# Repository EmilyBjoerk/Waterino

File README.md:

# Waterino

Waterino is a DIY multi-pot home watering system. Multiple pots are connected together by daisy chaining "nodes" together with a "root" node providing power, monitoring and water. The daisy chaining means that the chain can be re-ordered when moving pots around and that there is a minimal amount of wire-mess as opposed to a star-network.

Each "node" consists of an integrated moisture/temperature sensor and control logic, a pump/valve and an optional overflow sensor to safe guard from causing damage to the surrounding by watering too much.

The "root" node consists of a water reservoir, a Raspberry Pi and power delivery. The RPi monitors the nodes with heart-beat and listens for error reports over I2C, provides a web server with logging and monitoring and can be setup to send email alerts if an error is detected or if the water level in the reservoir is low.

# System Diagram

# Building on Debian
You'll need the following:

```sudo apt install build-essential git cmake clang clang-tools gcc-avr avr-libc libgmock-dev avrdude```

Building and running unit-tests:

```
cd firmware/test
mkdir build
cd build
cmake ..
make test
```

or ``` make && ./unit-tests ``` for a more detailed output.

Viewing code coverage of unit tests (first build as above):

```
cd firmware/test/build
../../codecov.sh [path_to_file.cpp]
```

Building binary:

```
cd firmware/src
mkdir build
cd build
cmake ..
make
```

Viewing binary stats (after building as above):

```
cd firmware/src/build
make size
make sizes
make disassemble && cat probe.lst
```

# Design
## Measurement
The Waterino uses capacitive soil moisture and temperature sensor integrated in the node PCB.

The PCB has a coplanar capacitor pattern where the soil is the dielectric. The capacitance of the coplanar capacitance depends on how much water is in the soil as the dielectric constant of water dominates that of other material in the soil. We measure the capacitance by charging it through a known resistance and measuring the time it takes to charge to a known value which gives the capacitance.

There is also a NTC thermistor inside the soil that we use to measure the soil temperature. The temperature is used for correcting the slight temperature dependency of the moisture-capacitance relation.

## Control
The user specifies the desired watering period in hours, the maximum time the pump may be active and the threshold moisture level when the pump will activate.
Each time the measured moisture drops below the threshold the pump activates. When the pump activates the onboard PID will measure the time from the last pump activation and use that in relation to the desired watering period to compute if it should give more or less water than it did last time.
Note that if a too long period is specified in relation to the water retaining capacity of the soil. It may be impossible to achieve the desired period. This would cause the PID give more and more water, causing the pot to eventually overflow. The maximum pump activation time is aimed at preventing this failure mode. 

## Logging
The node keeps a small in memory log of the last few measurements and other important information. The root will poll the nodes for their respective logs and keep a longer term history slice the data and serve it over HTTP.

## Communication
The node will print debug information over 5V UART at 38400 baud, 8 bits data, 0 parity, 1 stop bit.

The node is a i2c master and slave device. It can be addressed to read the log, set parameters and control the node in other ways. It can also send to the general call address and write a special magic sequence followed by it's own unique slave address, this acts as a mutex device for activating a pump so that only one pump is active at a time, thanks to the i2c bus arbitration and unique slave addresses. This is makes sure that the water preasure available is always the same for the pumps, one can imagine if all pumps were to activate at once, the feed line from the reservoir would probably not have enough flow rate and the later pumps in the daisy chain wouldn't get any water.

## Safety
There are a few things that can go wrong... First, it's an electronic device near water that can possibly output 12V@5A 60W of power. A number of safety measures are implemented to hopefully prevent the device from harming itself, you or the plants.
In no particular order:

* Nodes will detect if too much water was given to the plant by two electrodes which you put in the saucer below your plant. If these electrodes conduct electricity the pump is automatically killed and the node will limit the next pump activation to the time it took for it to overflow this time but make it 5% shorter. To prevent a fluke from limiting the pump activation to way too short times, it will carefully try to recover the maximum pump duration to the user set duration over time, backing off if it detects overflow again.
* It will detect if the water level in the reservoir is low and email you.
* It will prevent the time the pump is active from going below a minimum time.
* A PTC fuse on each node will trip if the power on that node shorts out, and a PTC fuse on the root will like wise protect the system.
* Nodes will detect upon restart if it was killed by the fuse tripping and emit a visual alert and push an error to the root. The node will resume normal operation after being power cycled once, allowing a human to inspect what went wrong before trying again.

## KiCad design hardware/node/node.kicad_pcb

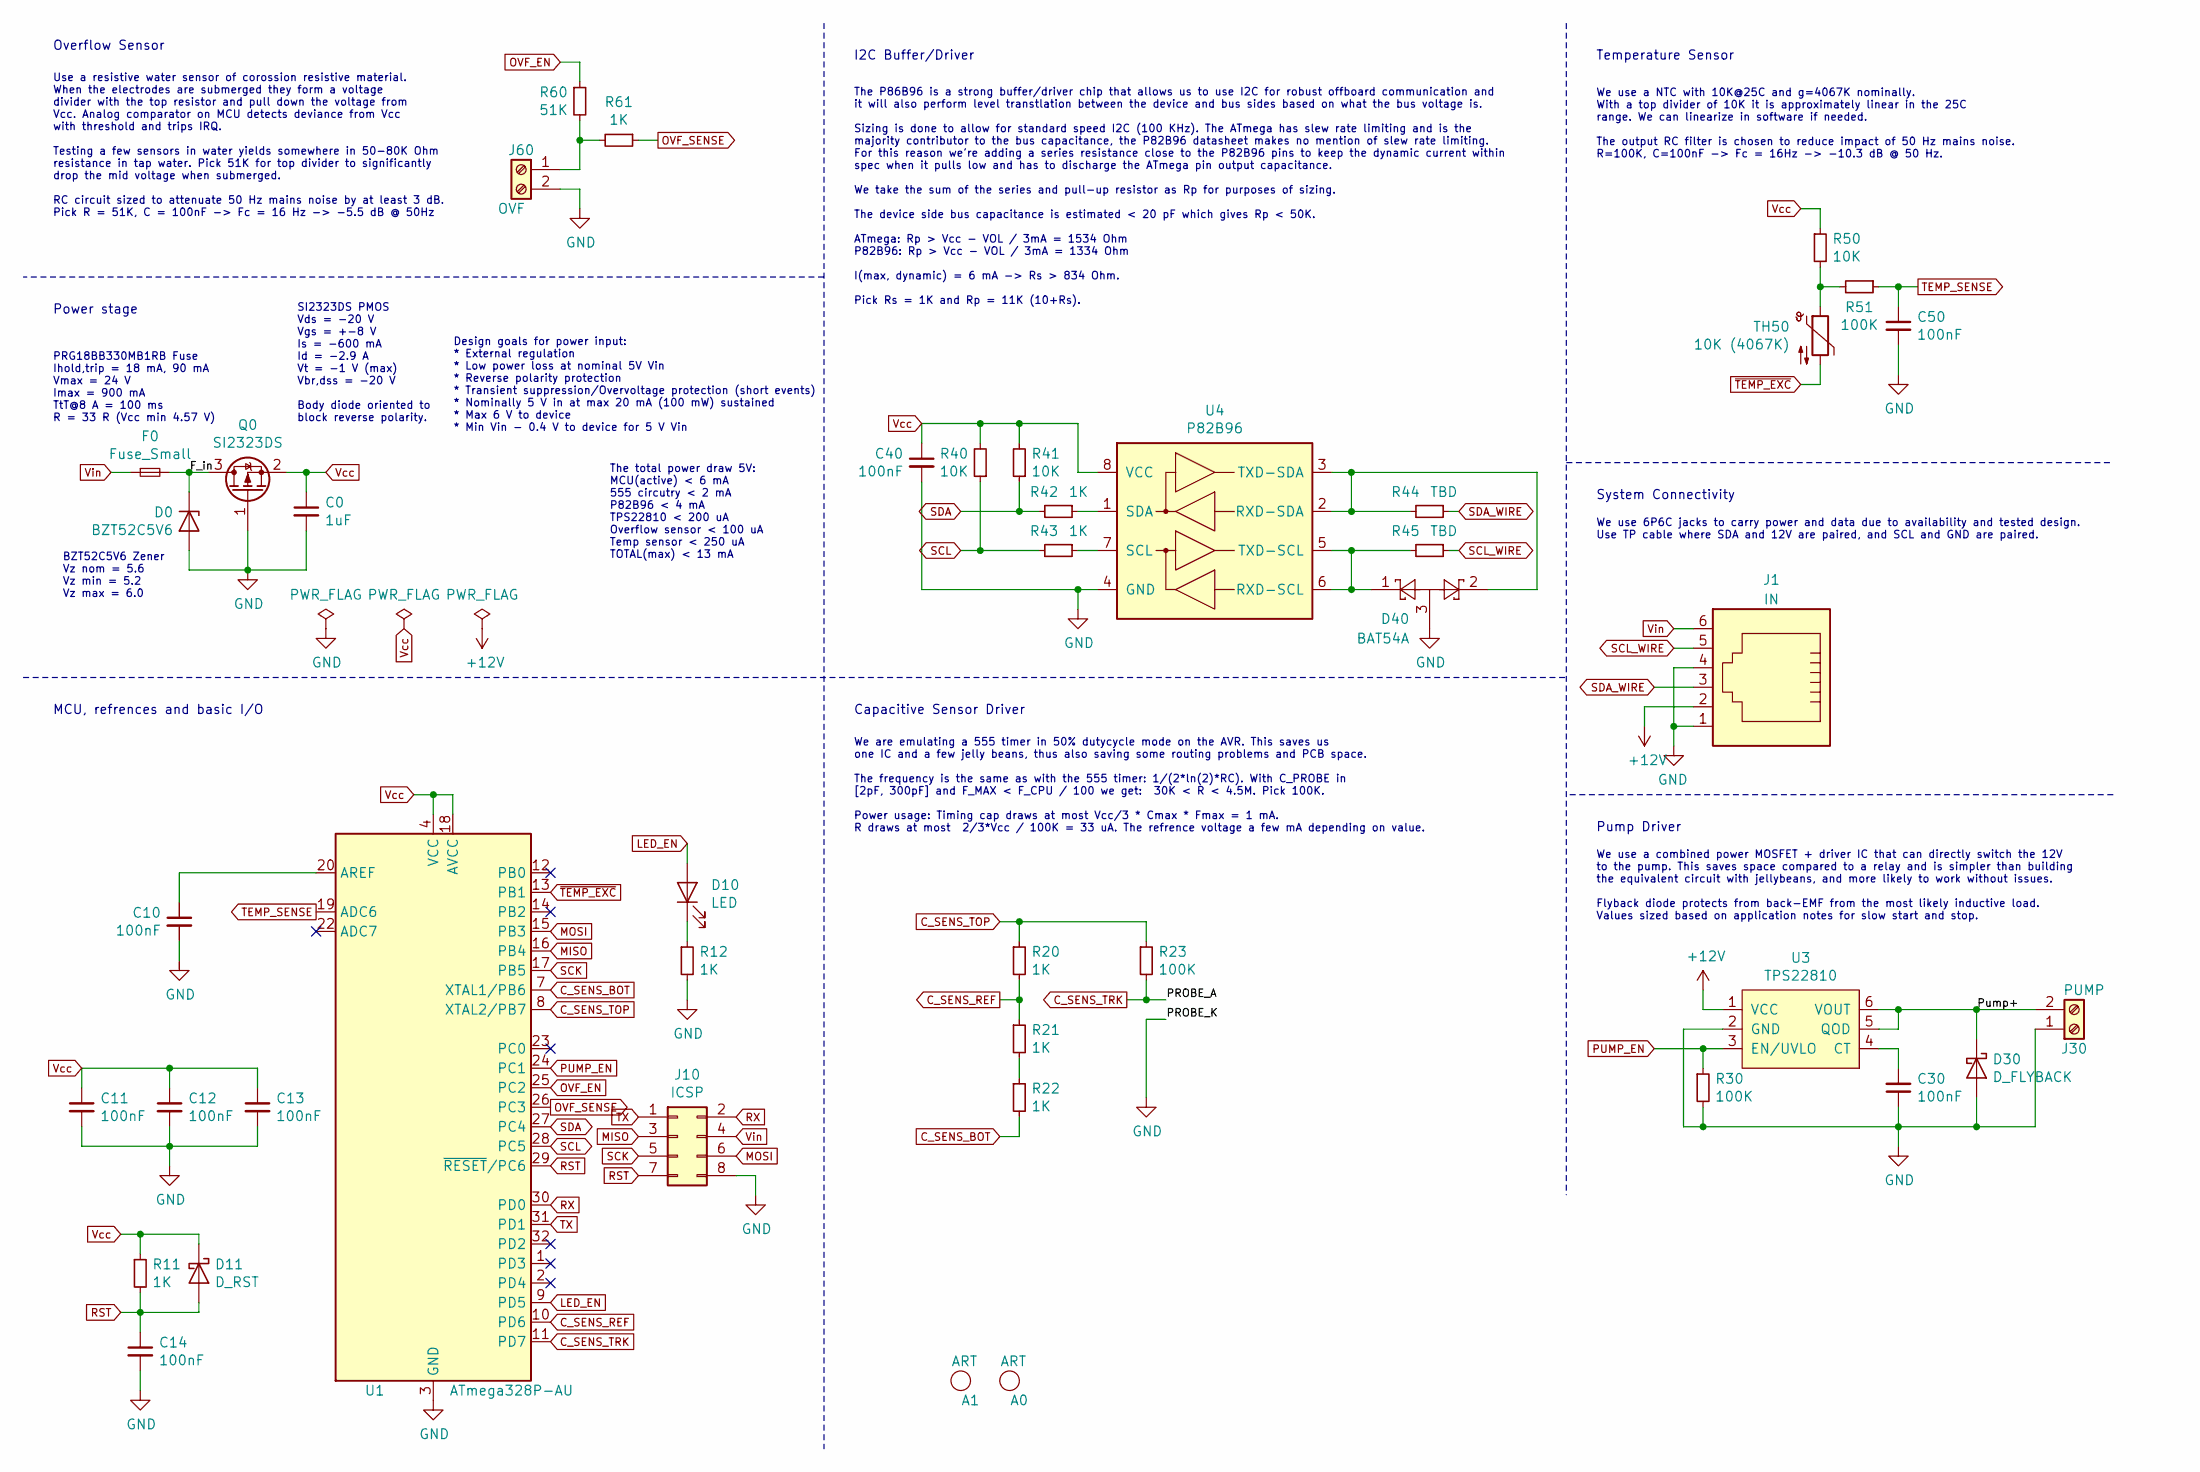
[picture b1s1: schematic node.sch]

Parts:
A0: ART; waterino_small_12_3mm
A1: ART; OSH_7_3mm
C0: 1uF; C_0603_1608Metric_Pad1.05x0.95mm_HandSolder
C10, C11, C12, C13, C14, C30, C40, C50: 100nF; C_0603_1608Metric_Pad1.05x0.95mm_HandSolder
D0: BZT52C5V6; D_SOD-123
D10: LED; LED_0603_1608Metric
D11: D_RST; D_SOD-123
D30: D_FLYBACK; D_SOD-123
D40: BAT54A; SOT-23
F0: Fuse_Small; Fuse_0603_1608Metric_Pad1.05x0.95mm_HandSolder
J1: IN; RJ12_Amphenol_54601
J10: ICSP; PinHeader_2x04_P2.54mm_Vertical
J30: PUMP; TerminalBlock_RND_205-00045_1x02_P5.00mm_Horizontal
J60: OVF; TerminalBlock_RND_205-00045_1x02_P5.00mm_Horizontal
Q0: SI2323DS; SOT-23W_Handsoldering
R11, R12, R20, R21, R22, R42, R43, R61: 1K; R_0603_1608Metric_Pad1.05x0.95mm_HandSolder
R23, R30, R51: 100K; R_0603_1608Metric_Pad1.05x0.95mm_HandSolder
R40, R41, R50: 10K; R_0603_1608Metric_Pad1.05x0.95mm_HandSolder
R44, R45: TBD; R_0603_1608Metric_Pad1.05x0.95mm_HandSolder
R60: 51K; R_0603_1608Metric_Pad1.05x0.95mm_HandSolder
TH50: 10K (4067K); R_0603_1608Metric_Pad1.05x0.95mm_HandSolder
U1: ATmega328P-AU; TQFP-32_7x7mm_P0.8mm
U3: TPS22810; SOT-23-6_Handsoldering
U4: P82B96; TSSOP-8_3x3mm_P0.65mm

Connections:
+12V: J1.2, U3.1 (VCC)
/F_in: D0.1 (K), F0.2, Q0.3 (D)
/Pump+: D30.1 (K), J30.2, U3.5 (QOD), U3.6 (VOUT)
C_SENS_BOT: R22.2, U1.7 (XTAL1/PB6)
C_SENS_REF: R20.2, R21.1, U1.10 (PD6)
C_SENS_TOP: R20.1, R23.1, U1.8 (XTAL2/PB7)
C_SENS_TRK: R23.2, U1.11 (PD7)
GND: C0.2, C10.2, C11.2, C12.2, C13.2, C14.2, C30.1, C40.2, C50.2, D0.2 (A), D30.2 (A), D40.3, J1.1, J1.4, J10.8, J30.1, J60.2, Q0.1 (G), R12.2, R30.2, U1.3 (GND), U1.5 (GND), U1.21 (GND), U3.2 (GND), U4.4 (GND)
LED_EN: D10.2 (A), U1.9 (PD5)
MISO: J10.3, U1.16 (PB4)
MOSI: J10.6, U1.15 (PB3)
unnamed: C10.1, U1.20 (AREF)
unnamed: C30.2, U3.4 (CT)
unnamed: D10.1 (K), R12.1
unnamed: D40.1, R45.2, U4.5 (TXD-SCL), U4.6 (RXD-SCL)
unnamed: D40.2, R44.2, U4.2 (RXD-SDA), U4.3 (TXD-SDA)
unnamed: J60.1, R60.2, R61.2
unnamed: R21.2, R22.1
unnamed: R42.1, U4.1 (SDA)
unnamed: R43.1, U4.7 (SCL)
unnamed: R50.2, R51.2, TH50.1
OVF_EN: R60.1, U1.25 (PC2)
OVF_SENSE: R61.1, U1.26 (PC3)
PUMP_EN: R30.1, U1.24 (PC1), U3.3 (EN/UVLO)
RST: C14.1, D11.2 (A), J10.7, R11.2, U1.29 (~RESET~/PC6)
RX: J10.2, U1.30 (PD0)
SCK: J10.5, U1.17 (PB5)
SCL: R40.1, R43.2, U1.28 (PC5)
SCL_WIRE: J1.5, R45.1
SDA: R41.1, R42.2, U1.27 (PC4)
SDA_WIRE: J1.3, R44.1
TEMP_SENSE: C50.1, R51.1, U1.19 (ADC6)
TX: J10.1, U1.31 (PD1)
Vcc: C0.1, C11.1, C12.1, C13.1, C40.1, D11.1 (K), Q0.2 (S), R11.1, R40.2, R41.2, R50.1, U1.4 (VCC), U1.6 (VCC), U1.18 (AVCC), U4.8 (VCC)
Vin: F0.1, J1.6, J10.4
~TEMP_EXC: TH50.2, U1.13 (PB1)

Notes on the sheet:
Power stage
Design goals for power input: * External regulation * Low power loss at nominal 5V Vin * Reverse polarity protection * Transient suppression/Overvoltage protection (short events) * Nominally 5 V in at max 20 mA (100 mW) sustained * Max 6 V to device * Min Vin - 0.4 V to device for 5 V Vin
BZT52C5V6 Zener Vz nom = 5.6 Vz min = 5.2 Vz max = 6.0
SI2323DS PMOS Vds = -20 V Vgs = +-8 V Is = -600 mA Id = -2.9 A Vt = -1 V (max) Vbr,dss = -20 V Body diode oriented to block reverse polarity.
PRG18BB330MB1RB Fuse Ihold,trip = 18 mA, 90 mA Vmax = 24 V Imax = 900 mA TtT@8 A = 100 ms R = 33 R (Vcc min 4.57 V)
We use 6P6C jacks to carry power and data due to availability and tested design. Use TP cable where SDA and 12V are paired, and SCL and GND are paired.
System Connectivity
Overflow Sensor
Use a resistive water sensor of corossion resistive material. When the electrodes are submerged they form a voltage divider with the top resistor and pull down the voltage from Vcc. Analog comparator on MCU detects deviance from Vcc with threshold and trips IRQ. Testing a few sensors in water yield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
Pump Driver
We use a combined power MOSFET + driver IC that can directly switch the 12V to the pump. This saves space compared to a relay and is simpler than building the equivalent circuit with jellybeans, and more likely to work without issues. Flyback diode protects from back-EMF from the most likely induct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
Temperature Sensor
We use a NTC with 10K@25C and g=4067K nominally. With a top divider of 10K it is approximately linear in the 25C range. We can linearize in software if needed. The output RC filter is chosen to reduce impact of 50 Hz mains noise. R=100K, C=100nF -> Fc = 16Hz -> -10.3 dB @ 50 Hz.
I2C Buffer/Driver
The P86B96 is a strong buffer/driver chip that allows us to use I2C for robust offboard communication and it will also perform level transtlation between the device and bus sides based on what the bus voltage is. Sizing is done to allow for standard speed I2C (100 KHz). The ATmega has slew rate lim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
Capacitive Sensor Driver
MCU, refrences and basic I/O
The total power draw 5V: MCU(active) < 6 mA 555 circutry < 2 mA P82B96 < 4 mA TPS22810 < 200 uA Overflow sensor < 100 uA Temp sensor < 250 uA TOTAL(max) < 13 mA
We are emulating a 555 timer in 50% dutycycle mode on the AVR. This saves us one IC and a few jelly beans, thus also saving some routing problems and PCB space. The frequency is the same as with the 555 timer: 1/(2*ln(2)*RC). With C_PROBE in [2pF, 300pF] and F_MAX < F_CPU / 100 we get: 30K < R < 4.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

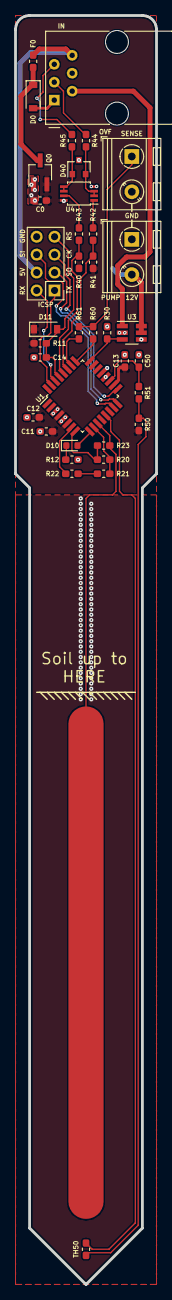
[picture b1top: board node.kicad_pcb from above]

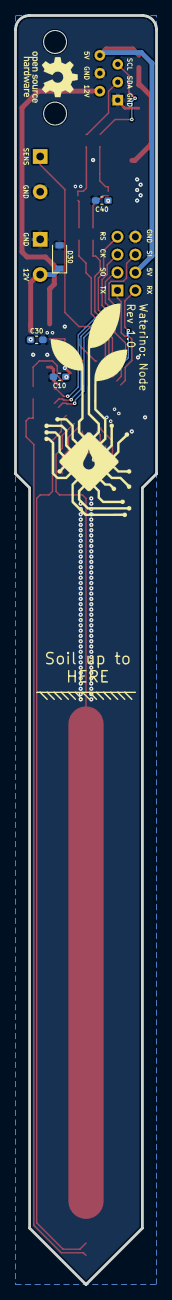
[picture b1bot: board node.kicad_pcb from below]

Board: 2 copper layers, 20.0 x 180.0 mm, 43 parts (6 on the bottom side), 36 nets.

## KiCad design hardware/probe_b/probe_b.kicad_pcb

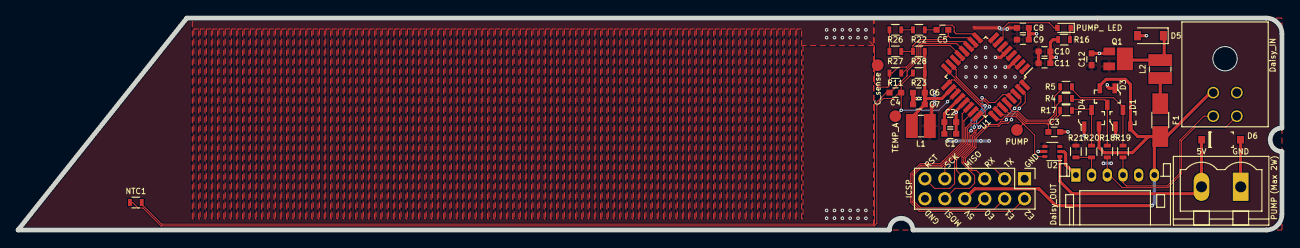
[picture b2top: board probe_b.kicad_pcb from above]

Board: 2 copper layers, 161.0 x 27.0 mm, 46 parts (0 on the bottom side), 37 nets.

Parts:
C1, C3, C6, C9, C10: 10nF; C_0603
C2, C4, C5, C7, C8, C11: 100nF; C_0603
C12: 1µF; C_0603
D1, D3, D4: BAT54S-7-F; SOT-23-3
D2: PUMP_ LED; D_0603
D5: BZT52C5V6; D_SOD-123
D6: MBR0520LT1G; SOD-123
F1: 0ZCJ0050FF2G; Fuse_SMD1206_HandSoldering
J1: ICSP; Pin_Header_Straight_2x06_Pitch2.54mm
J2: PUMP; Measurement_Point_Round-SMD-Pad_Small
J3: PUMP; PhoenixContact_MSTBVA-G_02x5.00mm_Vertical
J4: C_sense; Measurement_Point_Round-SMD-Pad_Small
J5: Daisy_OUT; JST_PH_S6B-PH-K_06x2.00mm_Angled
J6: Daisy_IN; Molex_Microfit3_Header_02x02_Angled_43045-040x
J7: TEMP_A; Measurement_Point_Round-SMD-Pad_Small
L1, L2: 10uH; 1210
NTC1: R; R_0603
Q1: SI2323DS; SOT-23-Power
R4, R5, R17, R18, R19, R20: 150R; R_0603
R11: 1M; R_0603
R16: 1K; R_0603
R21: 10K; R_0603
R22, R26, R27, R28: 100K; R_0603
R23: 15K; R_0603
U1: ATMEGA328P-AU; TQFP-32_7x7mm_Pitch0.8mm
U2: MIC94090; SOT-363_SC-70-6

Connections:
/Csense: J4.1, R11.2, U1.11
AVcc: C6.1, C7.1, L1.2, R23.1, R28.2, U1.18
DBG_A0: J1.6, U1.24
DBG_A1: J1.4, U1.23
DBG_A2: J1.2, U1.22
GND: C1.2, C2.2, C3.2, C6.2, C7.2, C8.2, C9.2, C10.2, C11.2, C12.2, D1.1, D3.1, D4.1, D5.2, D6.A, J1.1, J1.12, J3.1, J5.1, J5.5, J6.2, Q1.1, R16.2, U1.3, U1.5, U1.21, U2.2, U2.5
MISO: J1.7, U1.16
MOSI: J1.10, U1.15
unnamed: C1.1, C2.1, U1.20
unnamed: D1.3, R5.1, R19.2
unnamed: D2.1, R16.1
unnamed: D3.3, R4.1, R18.2
unnamed: D4.3, R17.1, R20.2
unnamed: D5.1, L2.2, Q1.3
unnamed: D6.K, J3.2, U2.1
unnamed: F1.2, L2.1
unnamed: J5.2, R20.1, R21.2
unnamed: J5.3, J6.4, R18.1
unnamed: J5.4, J6.3, R19.1
unnamed: R22.2, R26.1
unnamed: R26.2, R27.1
OVRFLW_SENSE: C3.1, R17.2, U1.26
PUMP: J2.1, U1.25, U2.6
PWRLED: D2.2, U1.7
RC_EN: R11.1, U1.12
RC_REF: C5.1, R27.2, R28.1, U1.10
RST: J1.11, U1.29
RX: J1.5, U1.30
SCK: J1.9, U1.17
SCL: R5.2, U1.28
SDA: R4.2, U1.27
TEMP+: C4.2, J7.1, NTC1.1, R23.2, U1.19
TX: J1.3, U1.31
Vcc: C8.1, C9.1, C10.1, C11.1, C12.1, L1.1, Q1.2, R21.1, U1.4, U1.6, U2.4
Vin: D1.2, D3.2, D4.2, F1.1, J1.8, J5.6, J6.1
~RC_EXC: C5.2, R22.1, U1.9
~TEMP_EXC: C4.1, NTC1.2, U1.13

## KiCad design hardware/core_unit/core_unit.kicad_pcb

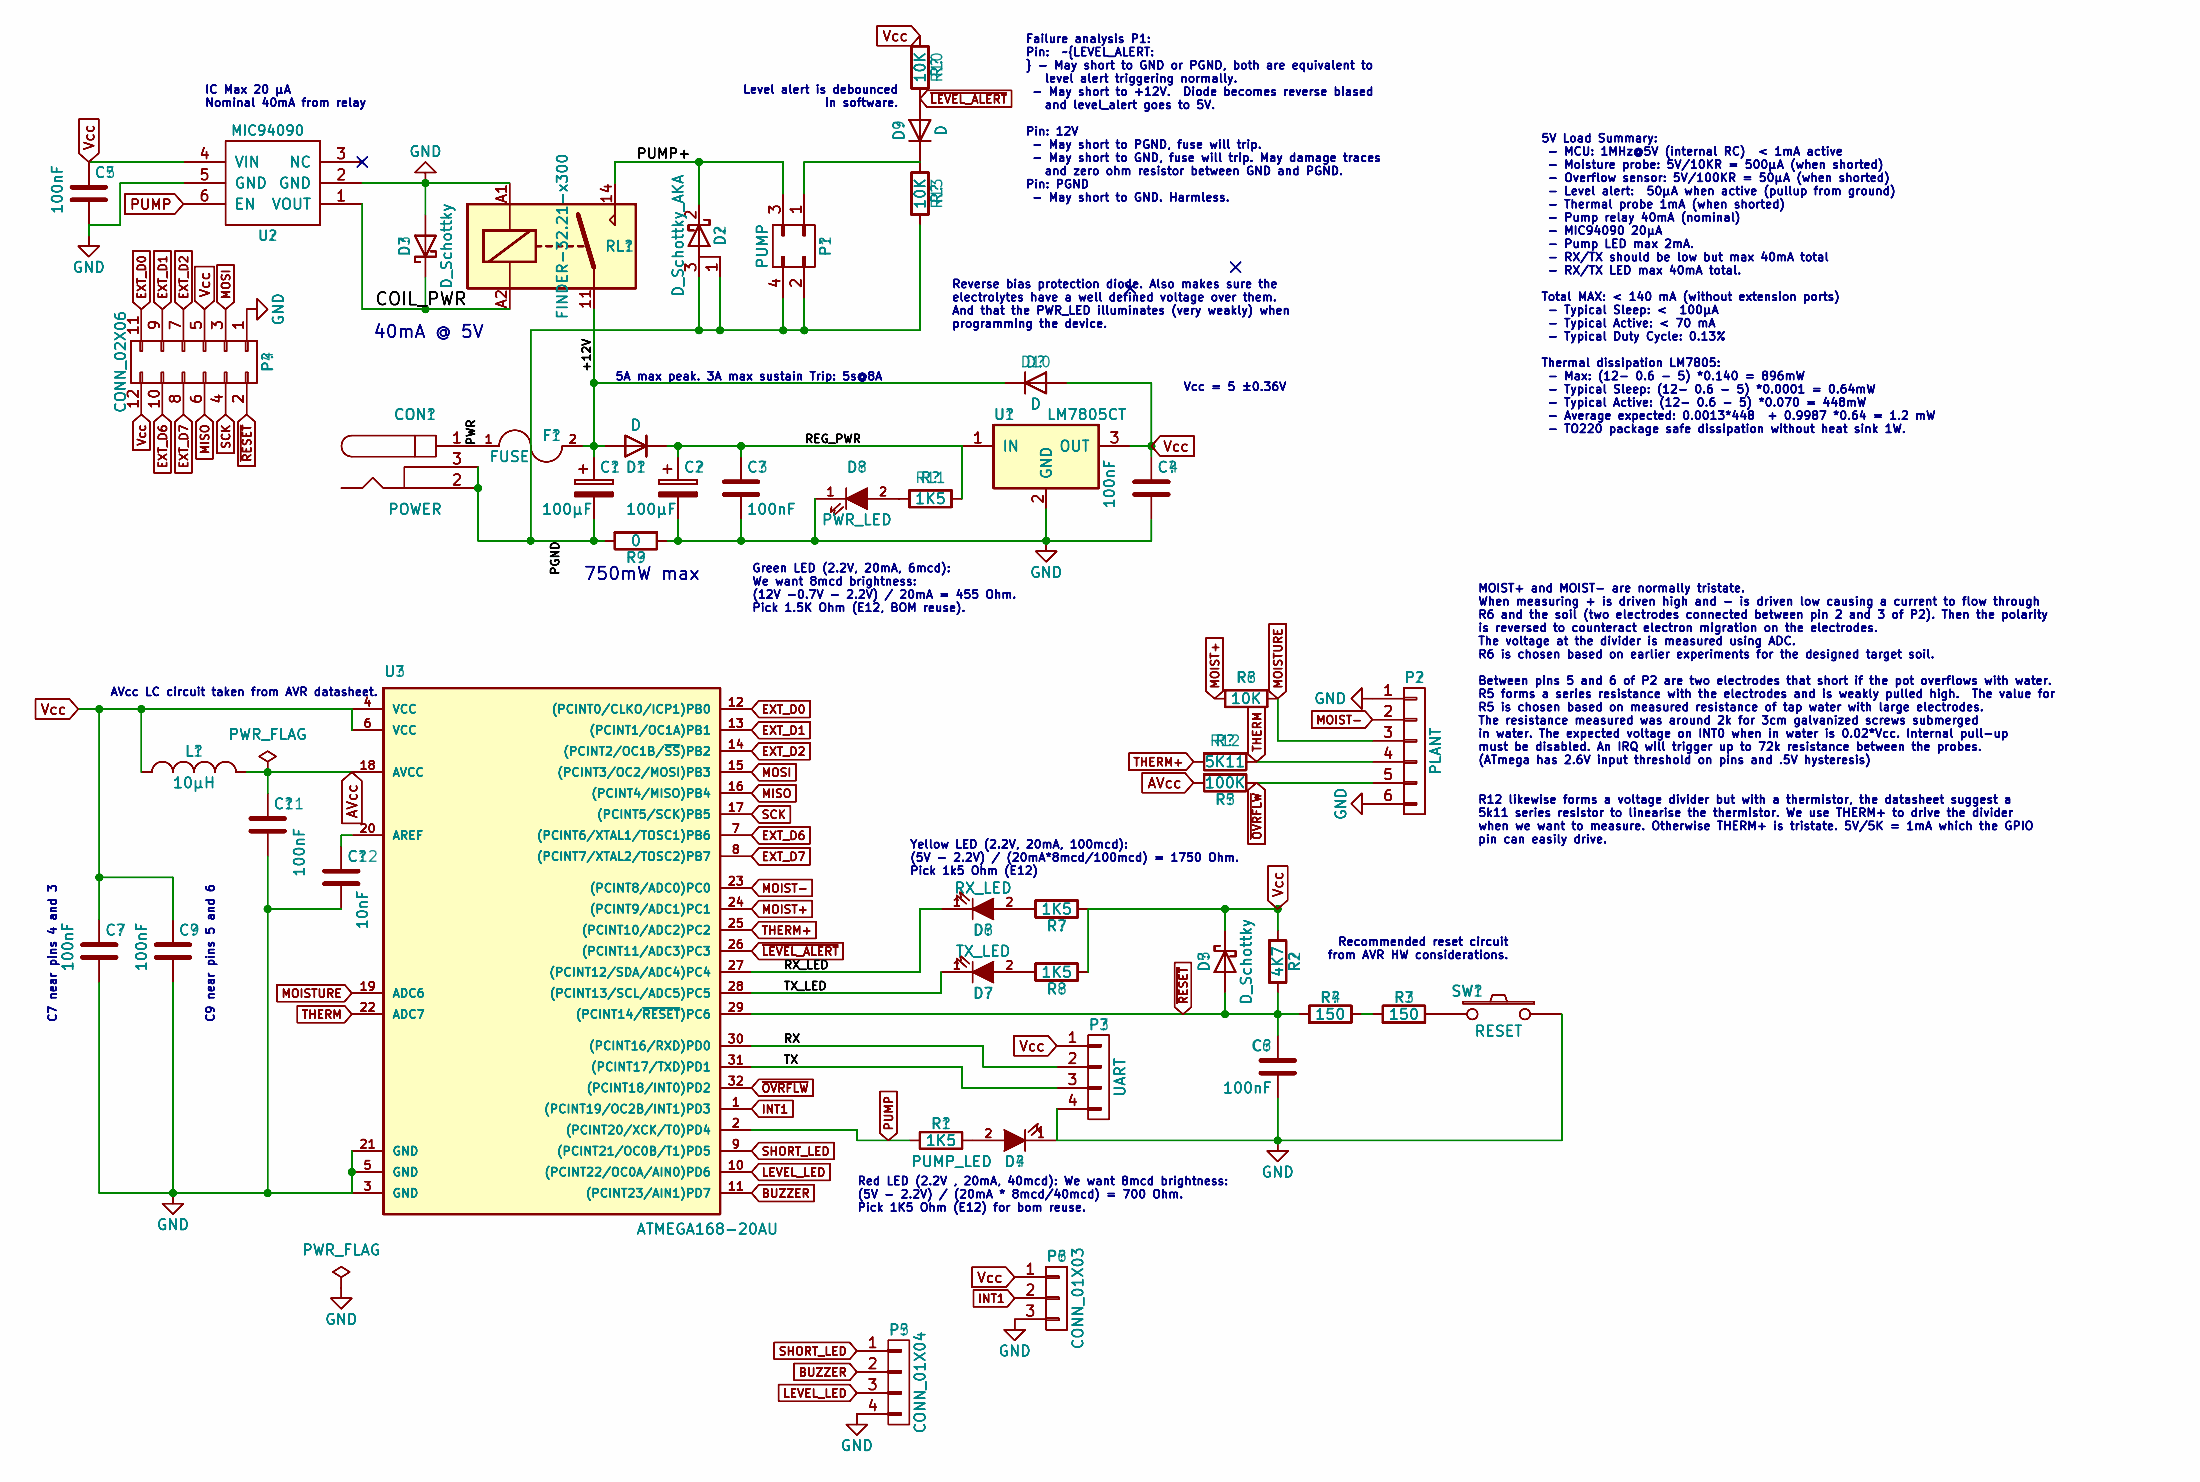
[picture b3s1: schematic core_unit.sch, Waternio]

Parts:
C1, C2: 100µF; CP_Elec_6.3x7.7
C3, C4, C5, C6, C7, C9, C11: 100nF; C_0603
C12: 10nF; C_0603
CON1: POWER; BARREL_JACK
D1, D9, D10: D; D_DO-41_SOD81_P7.62mm_Horizontal
D2: D_Schottky_AKA; TO-252-2_Rectifier
D3, D5: D_Schottky; D_SOD-123
D4: PUMP_LED; LED_0603
D6: RX_LED; LED_0603
D7: TX_LED; LED_0603
D8: PWR_LED; LED_0603
F1: FUSE; Fuse_SMD2920
L1: 10µH; L_Axial_L7.0mm_D3.3mm_P10.16mm_Horizontal_Fastron_MICC
P1: PUMP; Molex_Microfit3_Header_02x02_Angled_43045-040x
P2: PLANT; JST_PH_S6B-PH-K_06x2.00mm_Angled
P3: UART; Pin_Header_Straight_1x04_Pitch2.54mm
P4: CONN_02X06; Pin_Header_Straight_2x06_Pitch2.54mm
P5: CONN_01X04; Pin_Header_Straight_2x02_Pitch2.54mm
P6: CONN_01X03; Pin_Header_Straight_1x03_Pitch2.54mm
R1, R7, R8, R11: 1K5; R_0603
R2: 4K7; R_0603
R3, R4: 150; R_0603
R5: 100K; R_0603
R6, R10, R13: 10K; R_0603
R9: 0; R_2010
R12: 5K11; R_0603
RL1: FINDER-32.21-x300; Relay_SPST_Finder_32.21-x300
SW1: RESET; SW_PUSH_6mm
U1: LM7805CT; TO-220
U2: MIC94090; SOT-363_SC-70-6_Handsoldering
U3: ATMEGA168-20AU; TQFP-32_7x7mm_Pitch0.8mm

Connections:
/+12V: C1.1, D1.2 (A), D10.1 (K), F1.2, RL1.11
/COIL_PWR: D3.1 (K), RL1.A2, U2.1 (VOUT)
/PGND: C1.2, CON1.2, CON1.3, D2.1 (A), D2.3 (A), P1.2, P1.4, R9.2, R13.2
/PUMP+: D2.2 (K), P1.3, RL1.14
/PWR: CON1.1, F1.1
/REG_PWR: C2.1, C3.1, D1.1 (K), R11.1, U1.1 (IN)
/RX: P3.2, U3.30 ((PCINT16/RXD)PD0)
/RX_LED: D6.1 (K), U3.27 ((PCINT12/SDA/ADC4)PC4)
/TX: P3.3, U3.31 ((PCINT17/TXD)PD1)
/TX_LED: D7.1 (K), U3.28 ((PCINT13/SCL/ADC5)PC5)
AVcc: C11.1, L1.2, R5.2, U3.18 (AVCC)
BUZZER: P5.2, U3.11 ((PCINT23/AIN1)PD7)
EXT_D0: P4.11, U3.12 ((PCINT0/CLKO/ICP1)PB0)
EXT_D1: P4.9, U3.13 ((PCINT1/OC1A)PB1)
EXT_D2: P4.7, U3.14 ((PCINT2/OC1B/~SS~)PB2)
EXT_D6: P4.10, U3.7 ((PCINT6/XTAL1/TOSC1)PB6)
EXT_D7: P4.8, U3.8 ((PCINT7/XTAL2/TOSC2)PB7)
GND: C2.2, C3.2, C4.2, C5.2, C6.2, C7.2, C9.2, C11.2, C12.2, D3.2 (A), D4.1 (K), D8.1 (K), P2.1, P2.6, P3.4, P4.1, P5.4, P6.3, R9.1, RL1.A1, SW1.1, U1.2 (GND), U2.2 (GND), U2.5 (GND), U3.3 (GND), U3.5 (GND), U3.21 (GND)
INT1: P6.2, U3.1 ((PCINT19/OC2B/INT1)PD3)
LEVEL_LED: P5.3, U3.10 ((PCINT22/OC0A/AIN0)PD6)
MISO: P4.6, U3.16 ((PCINT4/MISO)PB4)
MOIST+: R6.1, U3.24 ((PCINT9/ADC1)PC1)
MOIST-: P2.2, U3.23 ((PCINT8/ADC0)PC0)
MOISTURE: P2.3, R6.2, U3.19 (ADC6)
MOSI: P4.3, U3.15 ((PCINT3/OC2/MOSI)PB3)
unnamed: C12.1, U3.20 (AREF)
unnamed: D4.2 (A), R1.2
unnamed: D6.2 (A), R7.2
unnamed: D7.2 (A), R8.2
unnamed: D8.2 (A), R11.2
unnamed: D9.1 (K), P1.1, R13.1
unnamed: R3.1, SW1.2
unnamed: R3.2, R4.1
PUMP: R1.1, U2.6 (EN), U3.2 ((PCINT20/XCK/T0)PD4)
SCK: P4.4, U3.17 ((PCINT5/SCK)PB5)
SHORT_LED: P5.1, U3.9 ((PCINT21/OC0B/T1)PD5)
THERM: P2.4, R12.1, U3.22 (ADC7)
THERM+: R12.2, U3.25 ((PCINT10/ADC2)PC2)
Vcc: C4.1, C5.1, C7.1, C9.1, D5.1 (K), D10.2 (A), L1.1, P3.1, P4.5, P4.12, P6.1, R2.2, R7.1, R8.1, R10.1, U1.3 (OUT), U2.4 (VIN), U3.4 (VCC), U3.6 (VCC)
~LEVEL_ALERT: D9.2 (A), R10.2, U3.26 ((PCINT11/ADC3)PC3)
~OVRFLW: P2.5, R5.1, U3.32 ((PCINT18/INT0)PD2)
~RESET: C6.1, D5.2 (A), P4.2, R2.1, R4.2, U3.29 ((PCINT14/~RESET~)PC6)

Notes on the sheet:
Yellow LED (2.2V, 20mA, 100mcd): (5V - 2.2V) / (20mA*8mcd/100mcd) = 1750 Ohm. Pick 1k5 Ohm (E12)
Green LED (2.2V, 20mA, 6mcd): We want 8mcd brightness: (12V -0.7V - 2.2V) / 20mA = 455 Ohm. Pick 1.5K Ohm (E12, BOM reuse).
MOIST+ and MOIST- are normally tristate. When measuring + is driven high and - is driven low causing a current to flow through R6 and the soil (two electrodes connected between pin 2 and 3 of P2). Then the polarity is reversed to counteract electron migration on the electrodes. The voltage at the d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
Red LED (2.2V , 20mA, 40mcd): We want 8mcd brightness: (5V - 2.2V) / (20mA * 8mcd/40mcd) = 700 Ohm. Pick 1K5 Ohm (E12) for bom reuse.
AVcc LC circuit taken from AVR datasheet.
40mA @ 5V
5V Load Summary: - MCU: 1MHz@5V (internal RC) < 1mA active - Moisture probe: 5V/10KR = 500µA (when shorted) - Overflow sensor: 5V/100KR = 50µA (when shorted) - Level alert: 50µA when active (pullup from ground) - Thermal probe 1mA (when shorted) - Pump relay 40mA (nominal) - MIC94090 20µA - Pump LE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
Level alert is debounced in software.
Recommended reset circuit from AVR HW considerations.
IC Max 20 µA Nominal 40mA from relay
C7 near pins 4 and 3
C9 near pins 5 and 6
Failure analysis P1: Pin: ~LEVEL_ALERT: - May short to GND or PGND, both are equivalent to level alert triggering normally. - May short to +12V. Diode becomes reverse biased and level_alert goes to 5V. Pin: 12V - May short to PGND, fuse will trip. - May short to GND, fuse will trip. May damage trac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
Vcc = 5 ±0.36V
750mW max
Reverse bias protection diode. Also makes sure the electrolytes have a well defined voltage over them. And that the PWR_LED illuminates (very weakly) when programming the device.
5A max peak. 3A max sustain Trip: 5s@8A

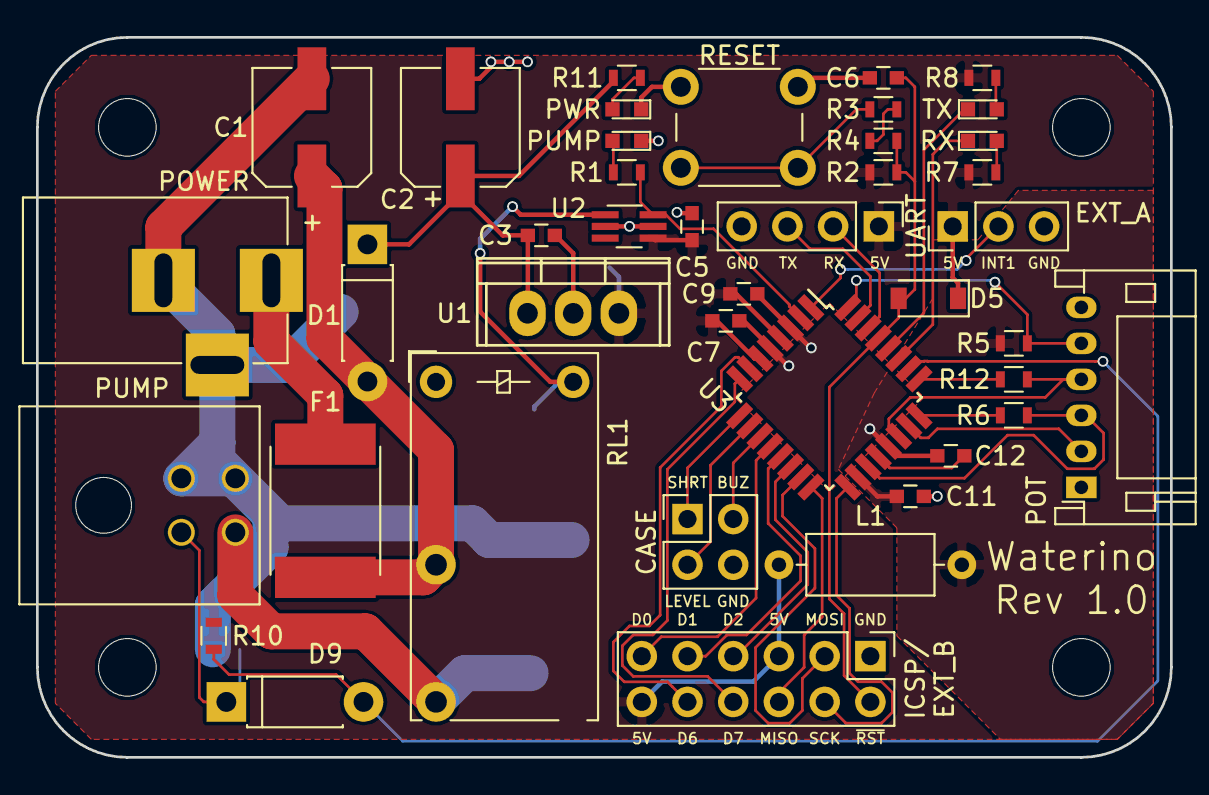
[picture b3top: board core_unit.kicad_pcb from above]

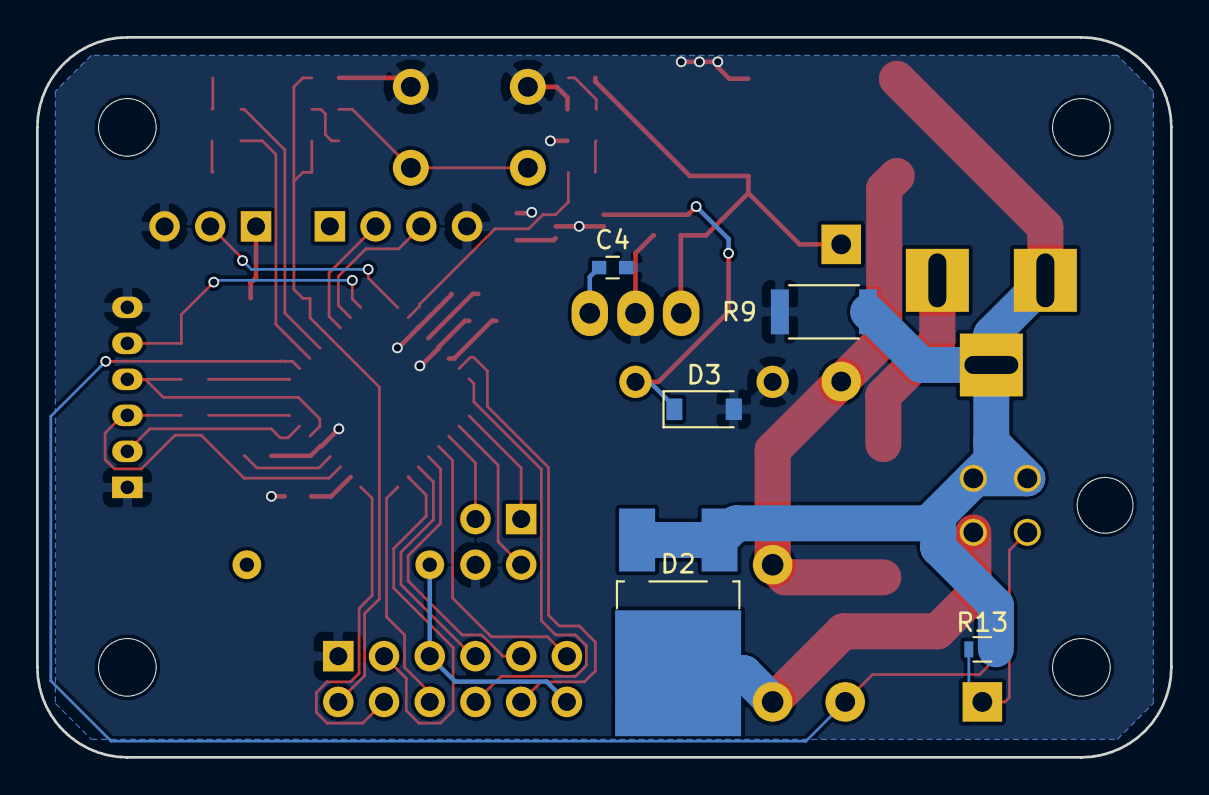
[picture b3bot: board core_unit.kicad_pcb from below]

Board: 2 copper layers, 63.0 x 40.0 mm, 50 parts (5 on the bottom side), 42 nets.

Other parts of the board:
MH_LL: MountingHole_3.2mm_M3
MH_LR: MountingHole_3.2mm_M3
MH_UL: MountingHole_3.2mm_M3
MH_UR: MountingHole_3.2mm_M3

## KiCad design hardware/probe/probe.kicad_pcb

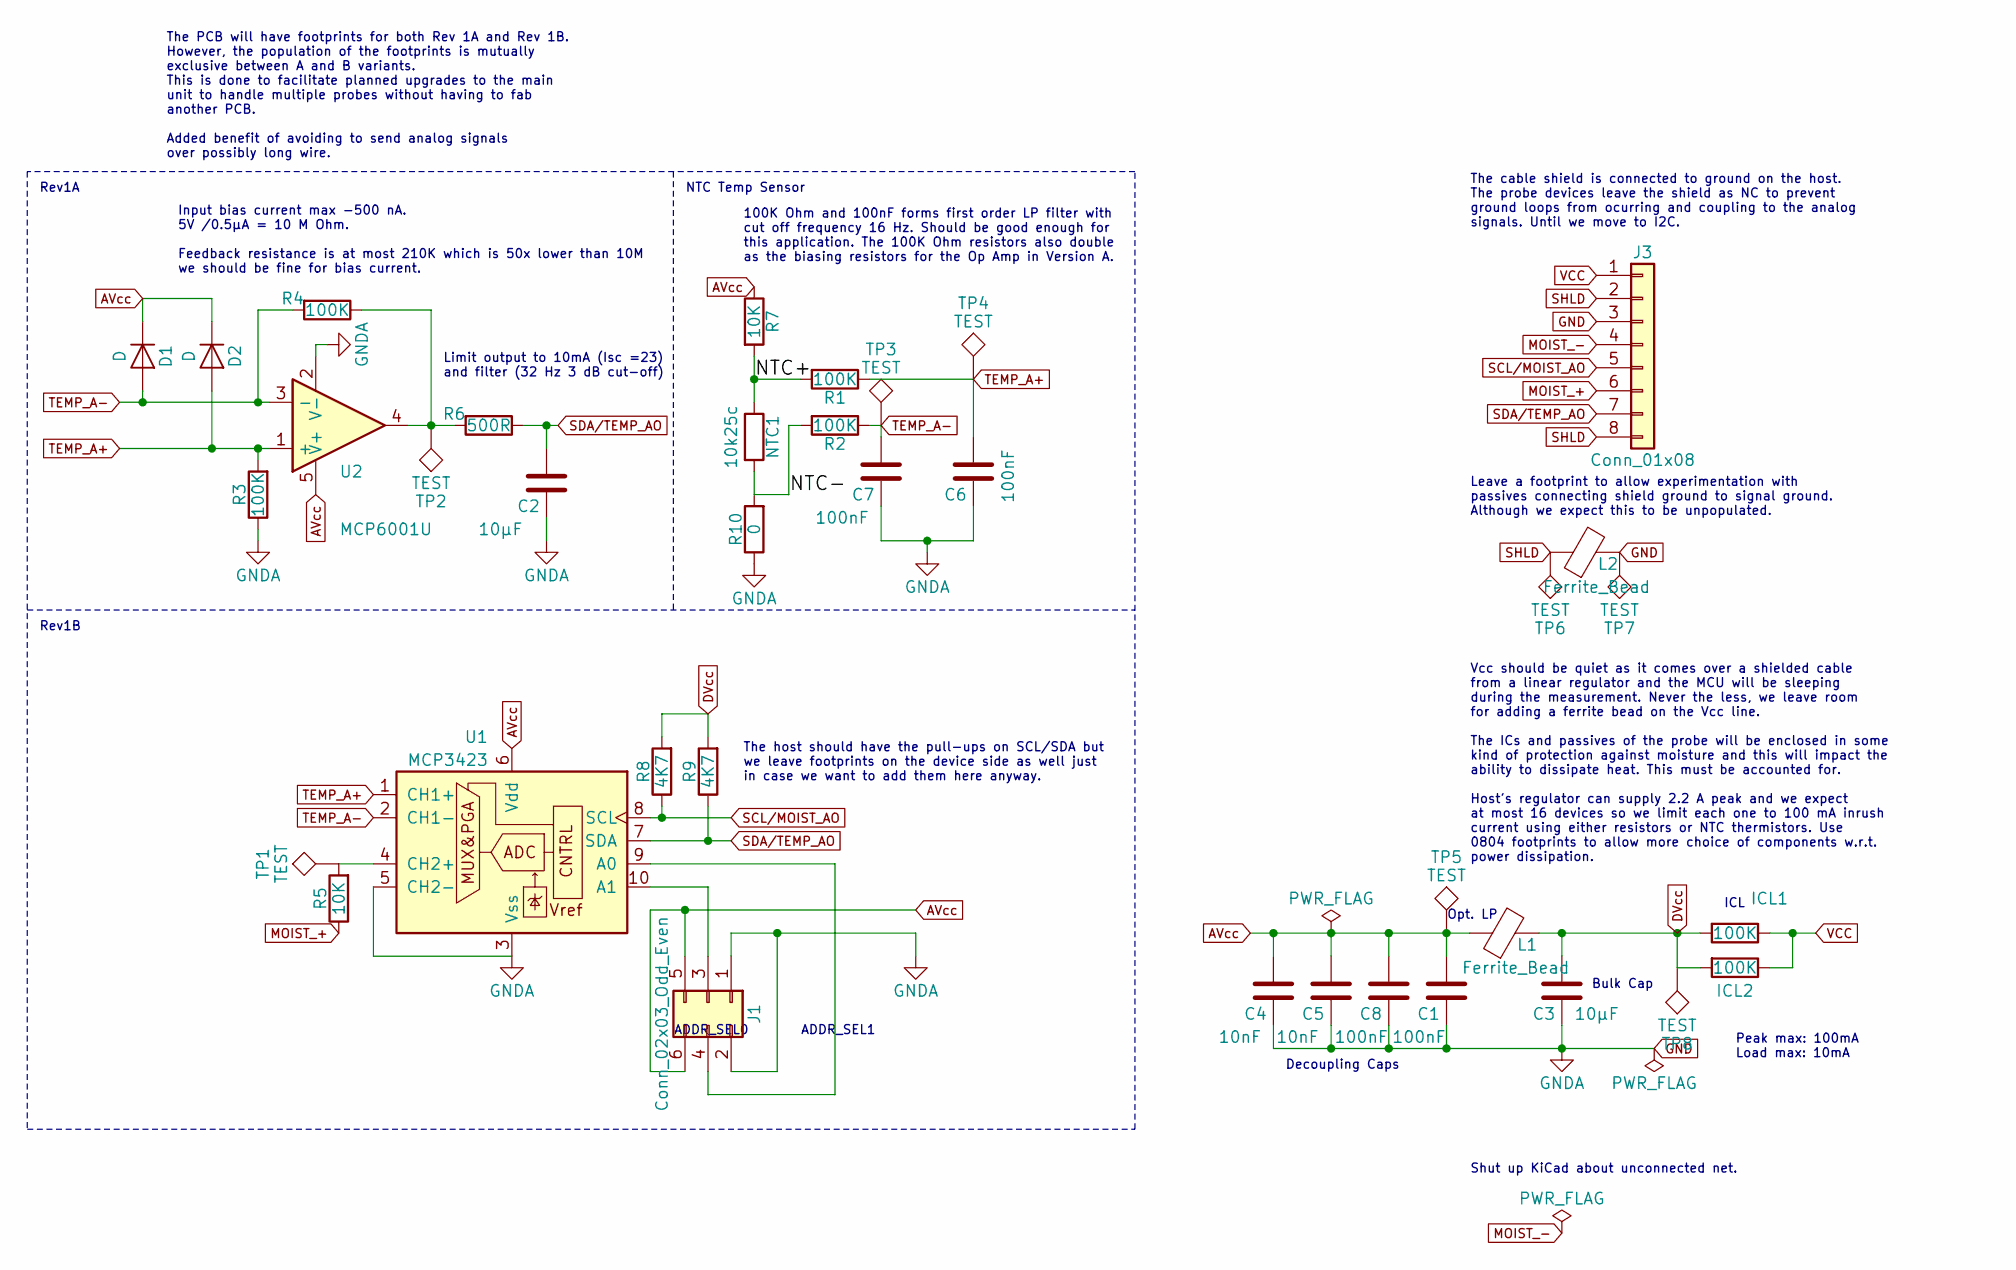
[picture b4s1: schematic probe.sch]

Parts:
C1, C6, C7, C8: 100nF; C_0603
C2, C3: 10µF; C_0603
C4, C5: 10nF; C_0603
D1, D2: D; D_SOD-123
ICL1, ICL2: 100K; R_0805
J1: Conn_02x03_Odd_Even; Pin_Header_Angled_2x03_Pitch2.54mm
J3: Conn_01x08; JST_PUD_S08B-PUDSS-1_2x04x2.00mm_Angled
L1, L2: Ferrite_Bead; R_0603
NTC1: 10k25c; R_0603
R1, R2, R3, R4: 100K; R_0603
R5, R7: 10K; R_0603
R6: 500R; R_0603
R8, R9: 4K7; R_0603
R10: 0; R_0603
TP1, TP2, TP3, TP4, TP5, TP6, TP7, TP8: TEST; Measurement_Point_Round-TH_Small
U1: MCP3423; MSOP-10_3x3mm_Pitch0.5mm
U2: MCP6001U; SOT-23-5

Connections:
/NTC+: NTC1.1, R1.2, R7.2
/NTC-: NTC1.2, R2.2, R10.2
AVcc: C1.2, C4.2, C5.2, C8.2, D1.1 (K), D2.1 (K), J1.5, J1.6, L1.1, R7.1, TP5.1, U1.6 (Vdd), U2.5 (V+)
DVcc: C3.2, ICL1.2, ICL2.2, L1.2, R8.2, R9.2, TP8.1
GND: C1.1, C2.1, C3.1, C4.1, C5.1, C6.1, C7.1, C8.1, J1.1, J1.2, J3.3, L2.2, R3.1, R10.1, TP7.1, U1.3 (Vss), U1.5 (CH2-), U2.2 (V-)
MOIST_+: J3.6, R5.1
MOIST_-: J3.4
unnamed: J1.3, U1.10 (A1)
unnamed: J1.4, U1.9 (A0)
unnamed: R4.1, R6.2, TP2.1, U2.4
unnamed: R5.2, TP1.1, U1.4 (CH2+)
SCL/MOIST_AO: J3.5, R8.1, U1.8 (SCL)
SDA/TEMP_AO: C2.2, J3.7, R6.1, R9.1, U1.7 (SDA)
SHLD: J3.2, J3.8, L2.1, TP6.1
TEMP_A+: C6.2, D2.2 (A), R1.1, R3.2, TP4.1, U1.1 (CH1+), U2.1 (+)
TEMP_A-: C7.2, D1.2 (A), R2.1, R4.2, TP3.1, U1.2 (CH1-), U2.3 (-)
VCC: ICL1.1, ICL2.1, J3.1

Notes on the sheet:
Rev1A
Rev1B
The PCB will have footprints for both Rev 1A and Rev 1B. However, the population of the footprints is mutually exclusive between A and B variants. This is done to facilitate planned upgrades to the main unit to handle multiple probes without having to fab another PCB. Added benefit of avoiding to s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
ADDR_SEL0
ADDR_SEL1
NTC Temp Sensor
The cable shield is connected to ground on the host. The probe devices leave the shield as NC to prevent ground loops from ocurring and coupling to the analog signals. Until we move to I2C.
Leave a footprint to allow experimentation with passives connecting shield ground to signal ground. Although we expect this to be unpopulated.
Vcc should be quiet as it comes over a shielded cable from a linear regulator and the MCU will be sleeping during the measurement. Never the less, we leave room for adding a ferrite bead on the Vcc line. The ICs and passives of the probe will be enclosed in some kind of protection against moisture 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
Bulk Cap
ICL
Opt. LP
Shut up KiCad about unconnected net.
Peak max: 100mA Load max: 10mA
Input bias current max -500 nA. 5V /0.5µA = 10 M Ohm. Feedback resistance is at most 210K which is 50x lower than 10M we should be fine for bias current.
Decoupling Caps
The host should have the pull-ups on SCL/SDA but we leave footprints on the device side as well just in case we want to add them here anyway.
100K Ohm and 100nF forms first order LP filter with cut off frequency 16 Hz. Should be good enough for this application. The 100K Ohm resistors also double as the biasing resistors for the Op Amp in Version A.
Limit output to 10mA (Isc =23) and filter (32 Hz 3 dB cut-off)

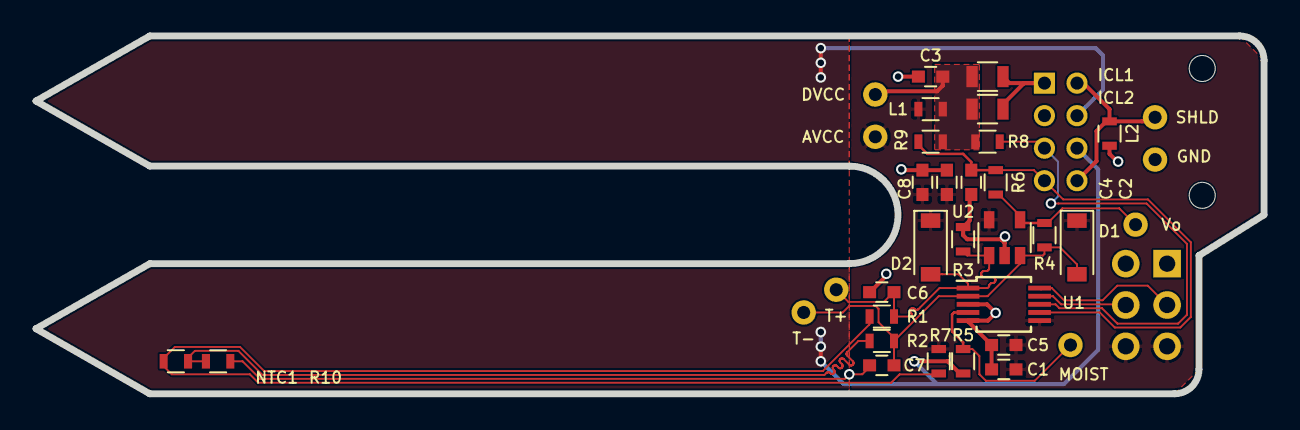
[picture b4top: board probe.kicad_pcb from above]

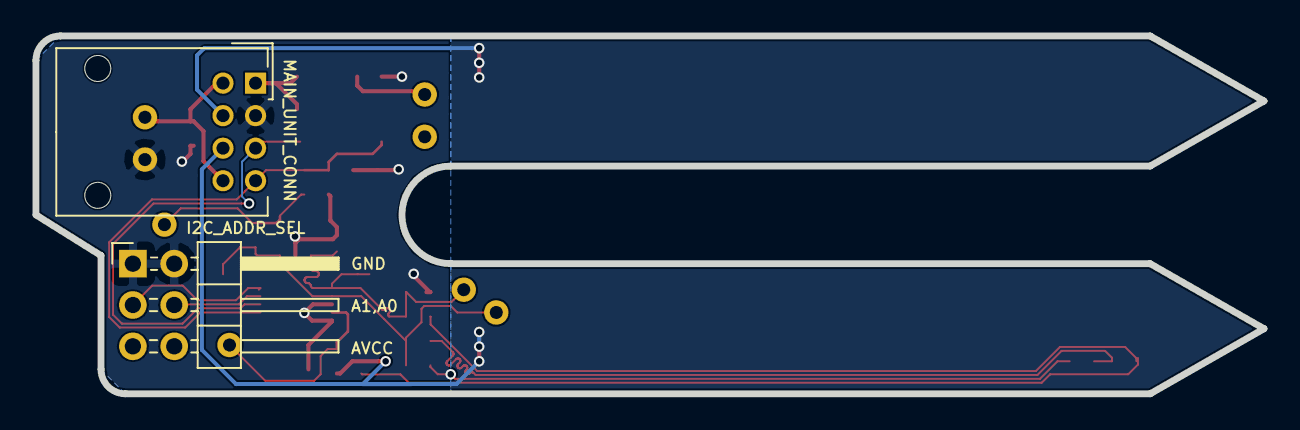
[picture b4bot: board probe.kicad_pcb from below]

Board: 2 copper layers, 75.5 x 22.0 mm, 37 parts (2 on the bottom side), 16 nets.
